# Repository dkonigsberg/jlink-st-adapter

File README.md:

# J-Link to STDC14 Adapter Board

This repository contains the [KiCad](http://kicad.org/) project
with the complete circuit schematics and PCB layout for an adapter
board used to connect cables designed for the STDC14 connector from
the [ST-Link v3](https://www.st.com/en/development-tools/stlink-v3set.html)
programmer to the port on a [Segger J-Link](https://www.segger.com/products/debug-probes/j-link/)
programmer.

Since the J-Link pinouts for SWD and JTAG modes are not directly
compatible, jumpers have been added for switching between them.
Also, since the J-Link's Virtual COM Port feature does not work
with JTAG mode, it has also been brought out to a pin header
so it can be connected to a serial adapter if desired.

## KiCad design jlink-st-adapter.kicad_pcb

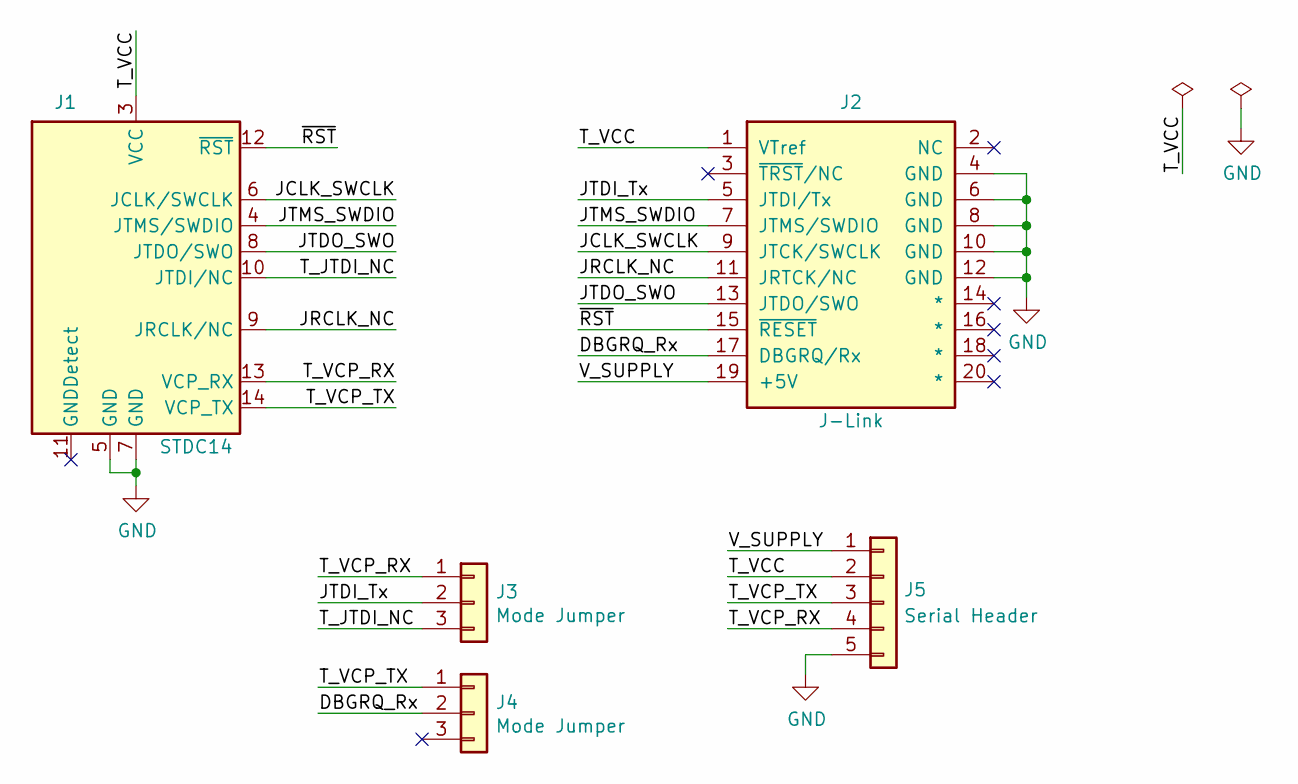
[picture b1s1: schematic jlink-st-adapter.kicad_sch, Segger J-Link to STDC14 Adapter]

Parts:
J1: STDC14; Samtec_FTSH-107-01-L-DV-K-A_2x07_P1.27mm; Manufacturer PN FTSH-107-01-L-DV-K-A
J2: J-Link; PinSocket_2x10_P2.54mm_Horizontal_Overhang; Manufacturer PN SFH11-PBPC-D10-RA-BK
J3, J4: Mode Jumper; PinHeader_1x03_P2.54mm_Vertical
J5: Serial Header; PinHeader_1x05_P2.54mm_Vertical

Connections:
/DBGRQ_Rx: J2.17 (DBGRQ/Rx), J4.2
/JCLK_SWCLK: J1.6 (JCLK/SWCLK), J2.9 (JTCK/SWCLK)
/JRCLK_NC: J1.9 (JRCLK/NC), J2.11 (JRTCK/NC)
/JTDI_Tx: J2.5 (JTDI/Tx), J3.2
/JTDO_SWO: J1.8 (JTDO/SWO), J2.13 (JTDO/SWO)
/JTMS_SWDIO: J1.4 (JTMS/SWDIO), J2.7 (JTMS/SWDIO)
/T_JTDI_NC: J1.10 (JTDI/NC), J3.3
/T_VCC: J1.3 (VCC), J2.1 (VTref), J5.2
/T_VCP_RX: J1.13 (VCP_RX), J3.1, J5.4
/T_VCP_TX: J1.14 (VCP_TX), J4.1, J5.3
/V_SUPPLY: J2.19 (+5V), J5.1
/~RST: J1.12 (~RST), J2.15 (~RESET)
GND: J1.5 (GND), J1.7 (GND), J2.4 (GND), J2.6 (GND), J2.8 (GND), J2.10 (GND), J2.12 (GND), J5.5

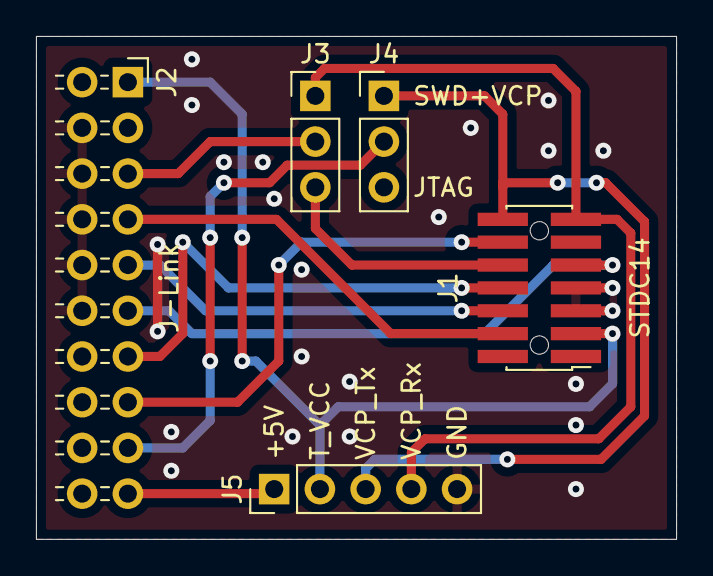
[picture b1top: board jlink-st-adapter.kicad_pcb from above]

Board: 2 copper layers, 35.6 x 27.9 mm, 5 parts (0 on the bottom side), 13 nets.

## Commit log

2021-12-24 Initial commit for J-Link to STDC14 adapter
2021-12-25 New files and updates for KiCad 6.0
2021-12-25 Removed legacy files
2021-12-25 More updates
2021-12-25 Updated ignore file
2021-12-25 Added basic docs
2021-12-25 Removed backup file
